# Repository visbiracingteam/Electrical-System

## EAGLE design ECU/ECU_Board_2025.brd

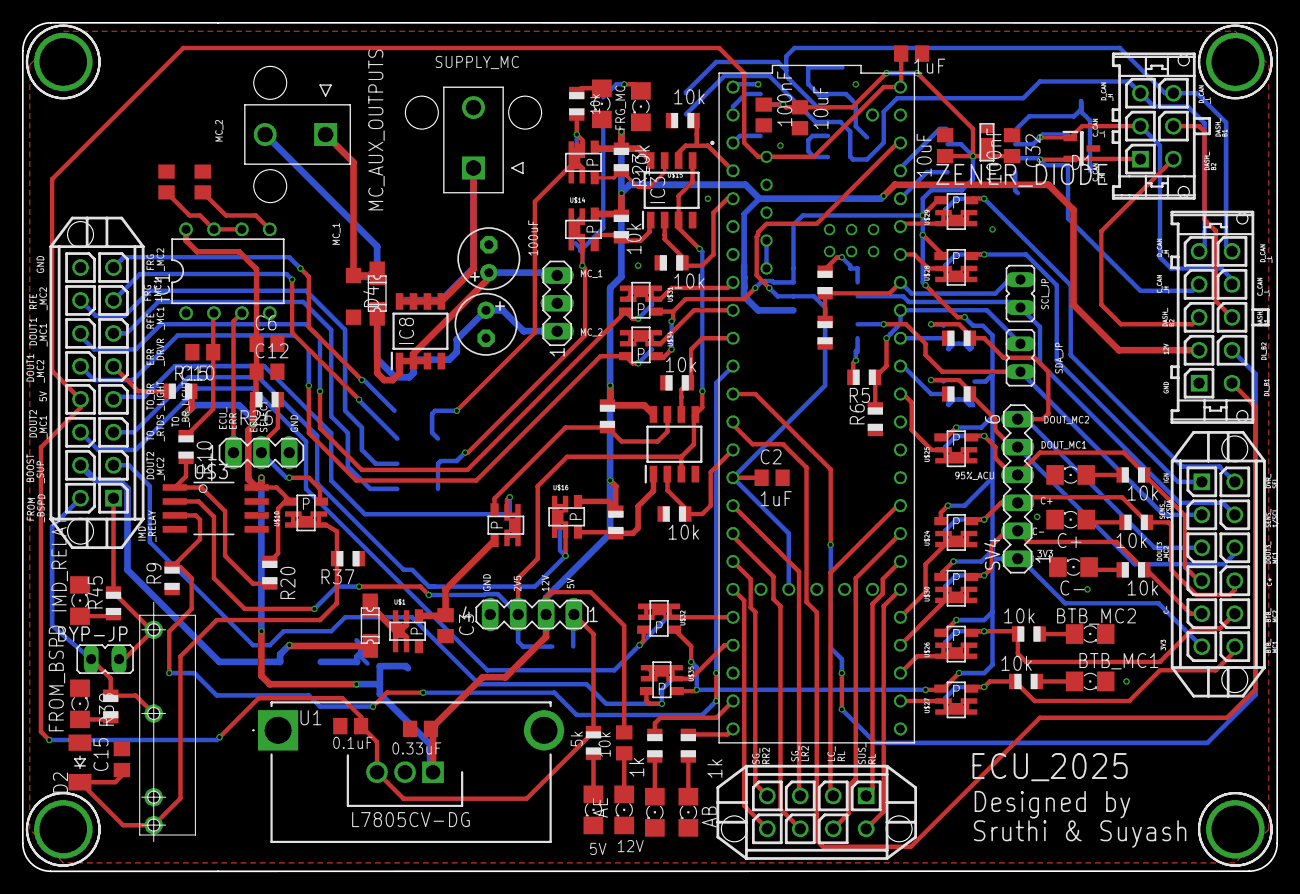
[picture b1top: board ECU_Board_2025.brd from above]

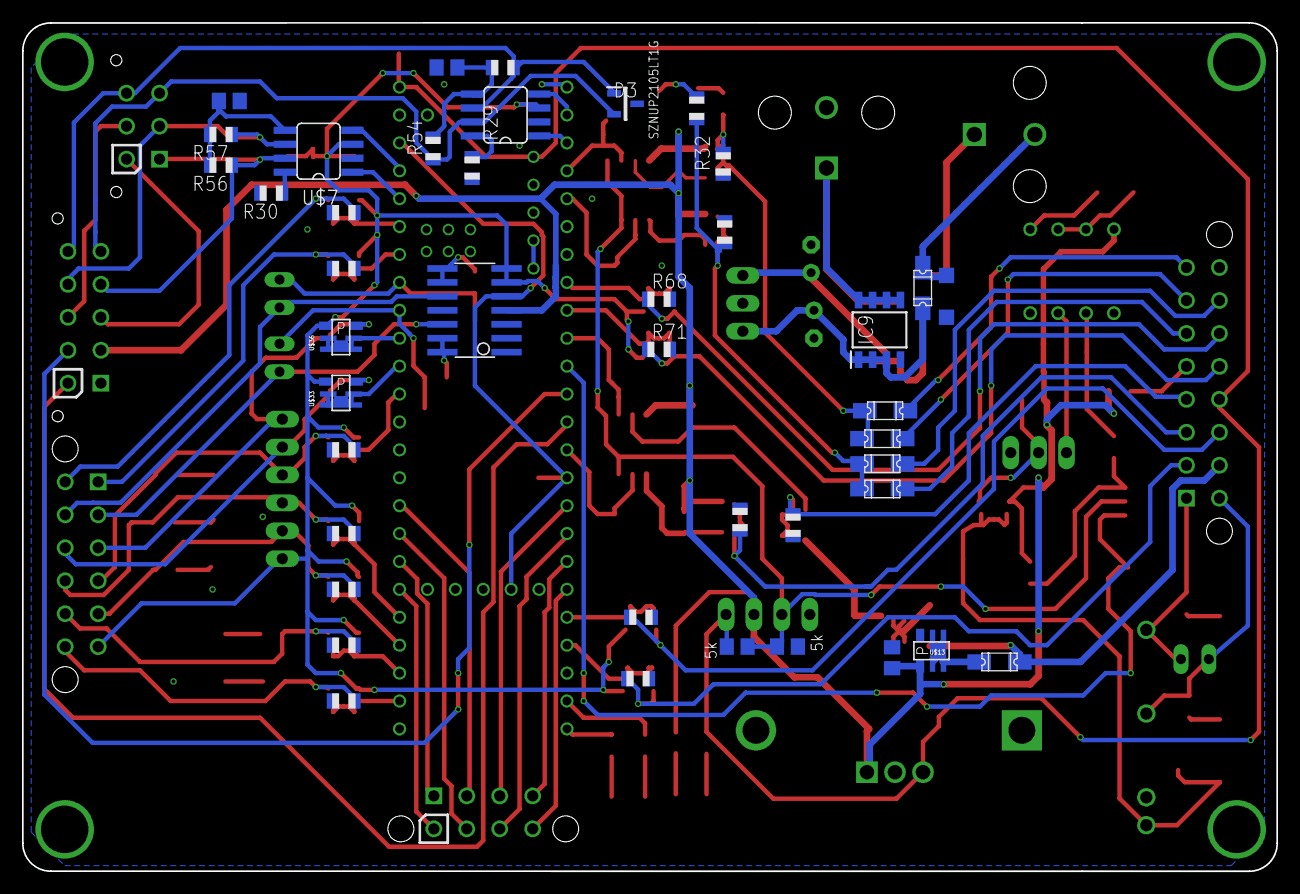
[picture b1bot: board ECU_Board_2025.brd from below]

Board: 2 copper layers, 114.2 x 77.2 mm, 150 parts (42 on the bottom side), 114 nets.

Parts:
5V, 12V: FKIT-LED-1206
>95%ACU: FKIT-LED-1206
AB: FKIT-LED-1206
AE: FKIT-LED-1206
BOOSTED_SUPPLY1: 172447-0002; 172447-YY02
BTB_MC1, BTB_MC2: FKIT-LED-1206
BYP-JP: JP1
C1, C2, C15: 1uF; C0805
C3, C4: C0805
C5, C35: 10uF; C0805
C6, C12, C13: 0.1uF; C0805
C7, C8: 100uF; E2,5-6
C10: 4.7uF; C0805
C11: 0.01uF; C0805
C32, C34: 100nF; C0805
C36, C37: 4n7F; C0805
C+: FKIT-LED-1206
C-: FKIT-LED-1206
D1, D3: SZNUP2105LT1G; SOT96P237X111-3N
D2: CGRM400-G; SOD-123_MINI-SMA
D4, D5: SOD123
DATA_LOGGER: 43045-1012
ECU_JPR: MA03-1
F1, F2, F3, F4, F5, F6, F7, F8: 1206L
FRG_MC: FKIT-LED-1206
FROM_BSPD: FKIT-LED-1206
IC1: LM555N; DIL08
IC2, IC3: NCV2903DR2G; SOIC127P600X175-8N
IC4: L7805CV-DG; TO255P460X1020X2008-3P
IC8, IC9: SI4425FDY-T1-GE3; SOIC127P600X175-8N
IMD_RELAY: FKIT-LED-1206
IN_CAP: 0.33uF; C0805
JP1, JP2: JP1
MC_AUX_OUTPUTS: 172447-0002; 172447-YY02
OUT_CAP: 0.1uF; C0805
R1, R7, R8, R9, R11, R12, R13, R14, R15, R16, R19, R22, R23, R24, R26, R27, R28, R31, R32, R34, R36, R38, R45, R52, R53: 10k; R0805
R2, R17, R21: 5k; R0805
R3, R5: 5K; R0805
R4, R6: 10K; R0805
R10: 200k; R0805
R20, R25, R33: 1k; R0805
R29, R30: 4k7; R0805
R37, R61, R62, R63, R64, R65, R66, R67, R68, R69, R70, R71, R72, R73: 100k; R0805
R54, R55, R56, R57: 60E; R0805
RFE_MC: FKIT-LED-1206
SV2: MA04-1
SV3: MA03-1
SV4: MA06-1
U1: HSS10-B20-P40; HSS10B20P40
U2: DEV-16771; MODULE_DEV-16771
U$1, U$10, U$13, U$14, U$15, U$16, U$17, U$24, U$25, U$26, U$27, U$28, U$29, U$30, U$31, U$32, U$33, U$34, U$35, U$36: TSOP-6_PMOS
U$2: LMC6464; SO14_LONGPADS
U$3: LMC6462; S08
U$7, U$8: SN65HVD230/1; SO8
U$9: G6DN_RELAY
U$20: ZENER_DIODE; SOD323HE
X1: 44769-0801
X2: 44769-1601
X3: 43045-0612
X4: 44769-1201

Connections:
2V5: IC2.3, IC2.5, IC3.3, IC3.5, R17.2, R21.1, SV2.3, U$3.2
3V3: C5.2, C32.2, C34.2, C35.2, SV4.1, U$2.6, U$2.7, U$7.3, U$8.3, U$20.CATHODE+, U$24.S, U$25.S, U$26.S, U$27.S, U$28.S, U$29.S, U$30.S, U$31.S, U$32.S, U$33.S, U$34.S, U$35.S, U$36.S, X4.P$6
3V3_TEENSY: C2.1, U2.3.3V_1, U2.3.3V_2, U2.3.3V_3, U$2.5
5V: C1.1, IC4.3, OUT_CAP.1, R2.2, R21.2, SV2.1, U2.5V, U2.VIN, X2.P$12
12V: C4.1, C6.1, C12.1, DATA_LOGGER.P$2, IC1.8, IC2.8, IC3.8, IC4.1, IN_CAP.1, R1.1, R15.2, R19.1, R20.1, R22.1, R23.1, R24.1, R26.2, SV2.2, U$2.4, U$3.8, U$10.S, U$13.S, U$14.S, U$15.S, U$16.S
>95%_ACU: R12.2, R66.1, SV4.4, U$25.G, X4.P$4
>95%_FINAL_3V3_INV: U2.15, U$25.1, U$25.2, U$25.5, U$25.6, U$25.D
AB: R25.2, U2.32
AE: R33.2, U2.31
AUXILIARY_VOLTAGE_MC1: D4.C, F3.P$1, MC_AUX_OUTPUTS.1
AUXILIARY_VOLTAGE_MC2: D5.C, F2.P$1, MC_AUX_OUTPUTS.2
BOOSTED_SUPPLY: F1.P$1, F8.P$1, X2.P$10
BR_LIGHT_SIG: IC2.6, R8.2, U2.8
BR_LIGHT_SUPPLY: C3.1, U$1.S, U$17.S
BTB_FROM_MC1: R27.2, R61.1, U$27.G, X4.P$12
BTB_FROM_MC1_3V3_INV: U2.34, U$27.1, U$27.2, U$27.5, U$27.6, U$27.D
BTB_FROM_MC2: R28.2, R62.1, U$26.G, X4.P$11
BTB_FROM_MC2_3V3_INV: U2.35, U$26.1, U$26.2, U$26.5, U$26.6, U$26.D
C+: R11.2, R63.1, SV4.3, U$24.G, X4.P$10
C+_3V3_INV: U2.37, U$24.1, U$24.2, U$24.5, U$24.6, U$24.D
C-: R13.2, R67.1, SV4.2, U$30.G, X4.P$5
C-_3V3_INV: U2.36, U$30.1, U$30.2, U$30.5, U$30.6, U$30.D
C_CAN_H: D1.2, DATA_LOGGER.P$4, R56.1, U$7.7, X3.P$1
C_CAN_L: D1.1, DATA_LOGGER.P$9, R57.1, U$7.6, X3.P$2
C_RX: U2.23, U$7.4
C_TX: U2.22, U$7.1
DASH_B1: DATA_LOGGER.P$8, X3.P$5
DASH_B2: DATA_LOGGER.P$3, X3.P$4
DL_B1: DATA_LOGGER.P$6, U2.11
DL_B2: DATA_LOGGER.P$7, U2.10
DOUT1_MC1: R68.1, U$31.G, X2.P$14
DOUT1_MC1_3V3: U2.6, U$31.1, U$31.2, U$31.5, U$31.6, U$31.D
DOUT1_MC2: R71.1, U$34.G, X2.P$13
DOUT1_MC2_3V3: U2.7, U$34.1, U$34.2, U$34.5, U$34.6, U$34.D
DOUT2_MC1: R69.1, U$32.G, X2.P$11
DOUT2_MC1_3V3: U2.28, U$32.1, U$32.2, U$32.5, U$32.6, U$32.D
DOUT2_MC2: R72.1, U$35.G, X2.P$2
DOUT2_MC2_3V3: U2.29, U$35.1, U$35.2, U$35.5, U$35.6, U$35.D
DOUT3_MC1: R70.1, SV4.5, U$33.G, X4.P$9
DOUT3_MC1_3V3: U2.16, U$33.1, U$33.2, U$33.5, U$33.6, U$33.D
DOUT3_MC2: R73.1, SV4.6, U$36.G, X4.P$3
DOUT3_MC2_3V3: U2.17, U$36.1, U$36.2, U$36.5, U$36.6, U$36.D
DRIVER_SELECT: R64.1, U$29.G, X4.P$7
DRIVER_SELECT_3V3_INV: U2.21, U$29.1, U$29.2, U$29.5, U$29.6, U$29.D
D_CAN_H: D3.2, DATA_LOGGER.P$5, R54.1, U$8.7, X3.P$3
D_CAN_L: D3.1, DATA_LOGGER.P$10, R55.1, U$8.6, X3.P$6
D_RX: U2.0, U$8.4
D_TX: U2.1, U$8.1
ECU_ERR: ECU_JPR.1, IC1.3
ECU_MC_ERR_SIG: R9.2, U2.9, U$3.3
ECU_SELECT: ECU_JPR.2, R26.1, U$10.G
ERR_RST_DRVR: R15.1, X2.P$5
FRG: IC3.6, R36.2, U2.2
FRG_MC: F4.P$1, F6.P$1, R16.2, R32.2, U$15.1, U$15.2, U$15.5, U$15.6, U$15.D
FRG_MC1: F6.P$2, X2.P$7
FRG_MC2: F4.P$2, X2.P$8
FROM_BSPD: BYP-JP.2, R38.2, U$9.P$3, X2.P$9
GND: 5V.C, 12V.C, >95%ACU.C, AB.C, AE.C, BOOSTED_SUPPLY1.2, BTB_MC1.C, BTB_MC2.C, C1.2, C2.2, C3.2, C4.2, C5.1, C6.2, C7.-, C8.-, C10.2, C11.2, C12.2, C13.2, C15.2, C32.1, C34.1, C35.1, C36.2, C37.2, C+.C, C-.C, D1.3, D2.A, D3.3, D4.A, D5.A, DATA_LOGGER.P$1, ECU_JPR.3, FRG_MC.C, FROM_BSPD.C, IC1.1, IC2.4, IC3.4, IC4.2, IC8.4, IC9.4, IMD_RELAY.C, IN_CAP.2, OUT_CAP.2, R4.1, R6.1, R7.1, R8.1, R9.1, R17.1, R29.2, R30.2, R31.1, R32.1, R34.1, R36.1, R37.1, R52.1, R53.1, R61.2, R62.2, R63.2, R64.2, R65.2, R66.2, R67.2, R68.2, R69.2, R70.2, R71.2, R72.2, R73.2, RFE_MC.C, SV2.4, U2.GND1, U2.GND2, U2.GND3, U2.GND4, U2.GND5, U$1.G, U$2.11, U$3.4, U$7.2, U$8.2, U$9.P$2, U$13.G, U$20.ANODE-, X2.P$16
IGNITION_SWITCH: R65.1, U$28.G, X4.P$1
IGNITION_SWITCH_3V3_INV: U2.20, U$28.1, U$28.2, U$28.5, U$28.6, U$28.D
IMD_RELAY: BYP-JP.1, R45.2, U$9.P$4, X2.P$1
LC_RL: U2.41, X1.P$2
LC_RR: U2.40, X1.P$6
MC_1: C7.+, F3.P$2, IC8.1, IC8.2, IC8.3, SV3.3
MC_2: C8.+, F2.P$2, IC9.1, IC9.2, IC9.3, SV3.1
unnamed: 12V.A, R1.2
unnamed: R14.1, RFE_MC.A
unnamed: AB.A, R25.1
unnamed: FRG_MC.A, R16.1
unnamed: IC2.1, R22.2, U$16.G
unnamed: 5V.A, R2.1
unnamed: IC2.7, R19.2, U$17.G
unnamed: AE.A, R33.1
unnamed: F8.P$2, U$1.1, U$1.2, U$1.5, U$1.6, U$1.D
unnamed: C10.1, IC1.2, R10.1
unnamed: C11.1, IC1.5
unnamed: R10.2, R20.2, U$3.1
unnamed: C+.A, R11.1
unnamed: >95%ACU.A, R12.1
unnamed: C-.A, R13.1
unnamed: BTB_MC1.A, R27.1
unnamed: C13.1, IC1.6, IC1.7
unnamed: IMD_RELAY.A, R45.1
unnamed: FROM_BSPD.A, R38.1
unnamed: BTB_MC2.A, R28.1
unnamed: R29.1, U$8.8
unnamed: C37.1, R54.2, R55.2, U$8.5
unnamed: C36.1, R56.2, R57.2, U$7.5
unnamed: R30.1, U$7.8
unnamed: F1.P$2, U$13.1, U$13.2, U$13.5, U$13.6, U$13.D
NET1: R3.2, U$2.8, U$2.9
NET2: R5.2, U$2.13, U$2.14
RFE: IC3.2, R34.2, U2.3
RFE_MC: F5.P$1, F7.P$1, R14.2, R31.2, U$14.1, U$14.2, U$14.5, U$14.6, U$14.D
RFE_MC1: F5.P$2, X2.P$6
RFE_MC2: F7.P$2, X2.P$15
RTDS_SIG: IC2.2, R7.2, U2.12
SENS_1/SCL: JP2.1, U$2.10, X4.P$8
SENS_1/SCL_OUT: JP2.2, R3.1, R4.2, U2.19
SENS_1/SDA: JP1.2, U$2.12, X4.P$2
SENS_1/SDA_OUT: JP1.1, R5.1, R6.2, U2.18
SG_LR1: U2.25, X1.P$7
SG_LR2: U2.24, X1.P$3
SG_RR1: U2.27, X1.P$8
SG_RR2: U2.26, X1.P$4
SUPPLY_MC: BOOSTED_SUPPLY1.1, IC8.5, IC8.6, IC8.7, IC8.8, IC9.5, IC9.6, IC9.7, IC9.8
SUS_RL: U2.39, X1.P$1
SUS_RR: U2.38, X1.P$5
TO_BR_LIGHT: R53.2, U$17.1, U$17.2, U$17.5, U$17.6, U$17.D, X2.P$4
TO_ECU_RELAY: C15.1, D2.C, R37.2, U$9.P$1, U$10.1, U$10.2, U$10.5, U$10.6, U$10.D
TO_FRG_ENABLE: IC3.7, R23.2, U$15.G
TO_RFE_ENABLE: IC3.1, R24.2, U$14.G
TO_RTDS: R52.2, U$16.1, U$16.2, U$16.5, U$16.6, U$16.D, X2.P$3
USB_GND: U2.USB_GND1, U2.USB_GND2

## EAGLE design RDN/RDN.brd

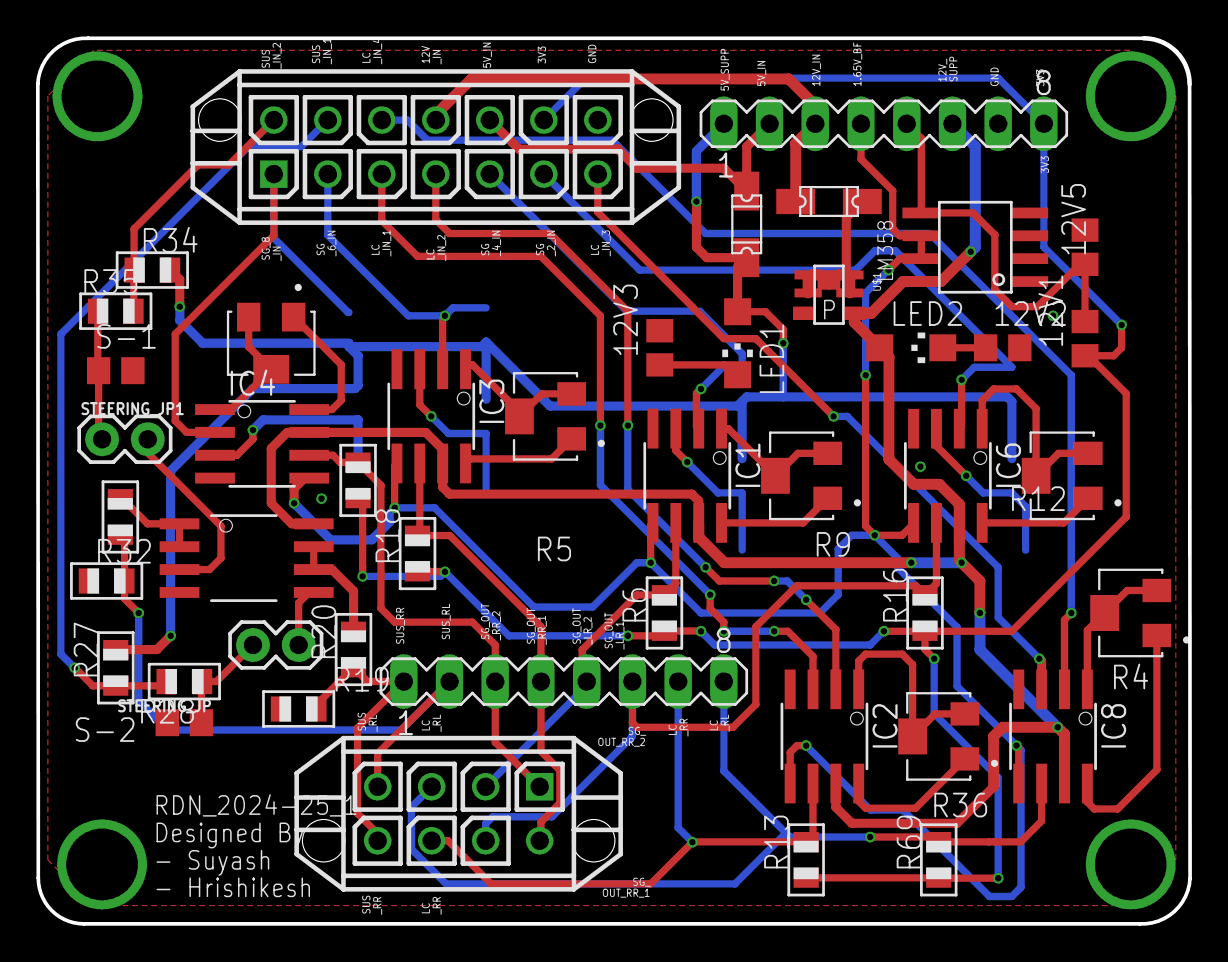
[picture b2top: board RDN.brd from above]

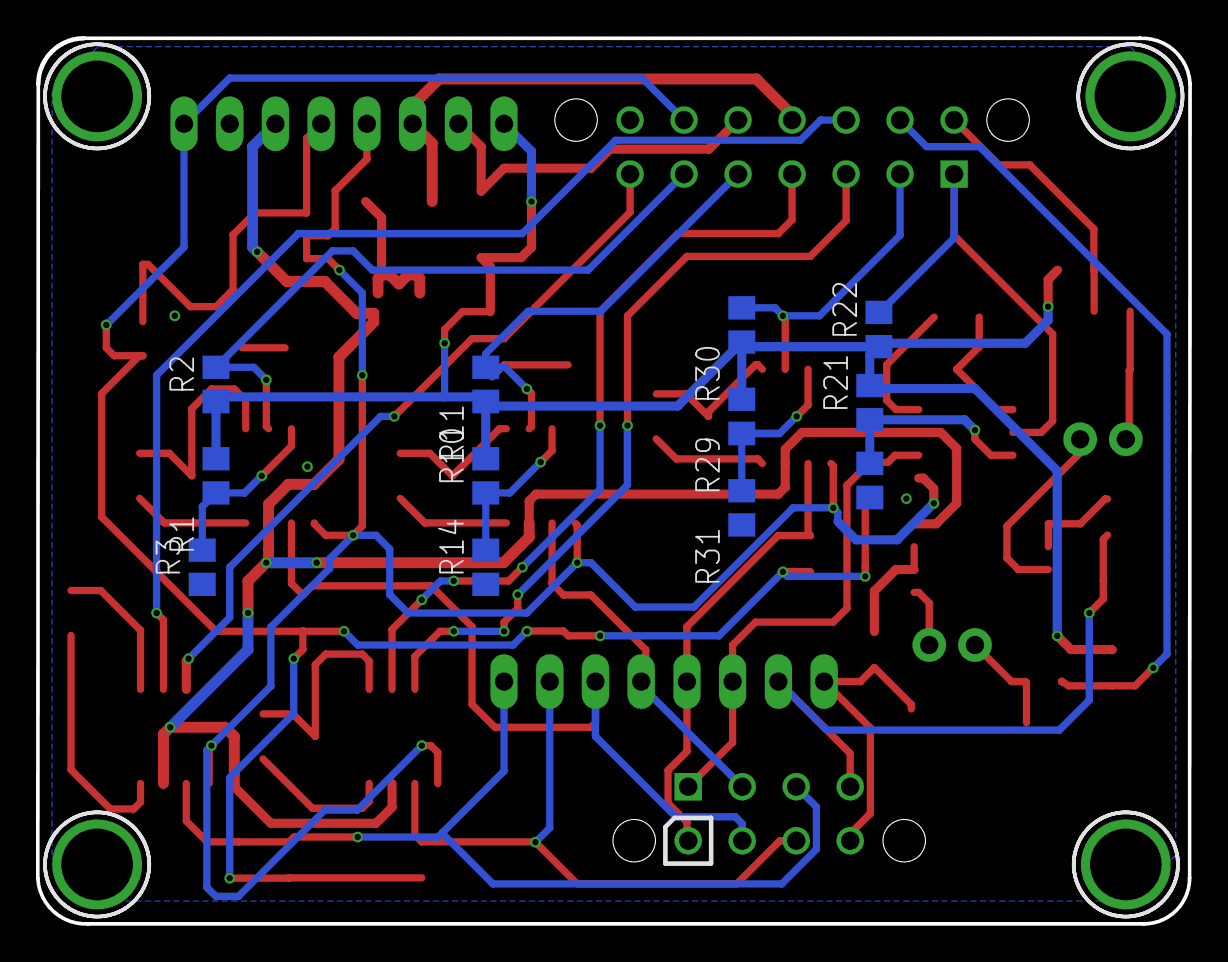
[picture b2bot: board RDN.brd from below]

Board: 2 copper layers, 64.0 x 49.2 mm, 57 parts (12 on the bottom side), 51 nets.

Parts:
12V1, 12V5: 10k; R0805
12V2: 2k; R0805
12V3: 6k; R0805
F1, F5: 1206L
IC1, IC2, IC3, IC4, IC6, IC8: INA122U; SO08
LED1, LED2: CHIPLED_1206
LM358: LM358EDR2G; SOIC-8
R1, R2, R3, R10, R11, R14, R21, R22, R23, R29, R30, R31: 120; R0805
R4, R5, R7, R9, R12, R36: PVG5A103C03R00; TRIM_PVG5A103C03R00
R6, R13, R16, R18, R26, R28, R35, R69: 1k; R0805
R19, R32: 10k; R0805
R20, R33: 5k; R0805
R27, R34: 300k; R0805
S-1, S-2: 1uF; C0805
STEERING_JP, STEERING_JP1: STEERING_JP; 1X02
SV1, SV4: MA08-1
U$1: TSOP-6_PMOS
U$2: LMC6462; S08
X3: 44769-0801
X4: 44769-1401

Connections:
1.65V_REF: 12V1.2, 12V5.1, LM358.5, SV1.5
1.65V_REF_BF: IC1.5, IC2.5, IC3.5, IC4.5, IC6.5, IC8.5, LM358.6, LM358.7, SV1.4
3V3: 12V1.1, R6.1, R13.1, R16.1, R18.1, R26.1, R69.1, SV1.8, X4.P$13
5V_IN: F5.P$2, SV1.2, X4.P$12
5V_SUPPLY: F5.P$1, LED1.A, R1.2, R2.1, R10.2, R11.1, R21.2, R22.1, R27.2, R29.2, R30.1, R34.2, SV1.1
12V_IN: F1.P$2, SV1.3, X4.P$11
12V_SUPPLY: IC1.7, IC2.7, IC3.7, IC4.7, IC6.7, IC8.7, LED2.A, LM358.8, SV1.6, U$1.S, U$2.8
GND: 12V2.2, 12V3.2, 12V5.2, IC1.4, IC2.4, IC3.4, IC4.4, IC6.4, IC8.4, LM358.4, R3.1, R14.1, R19.1, R23.1, R31.1, R32.1, S-1.2, S-2.2, SV1.7, U$1.G, U$2.4, X4.P$14
LC_RL: IC8.6, R69.2, SV4.8, X3.P$3
LC_RR: IC2.6, R13.2, SV4.7, X3.P$7
LOADCELL_IN_1: IC2.3, X4.P$3
LOADCELL_IN_2: IC2.2, X4.P$4
LOADCELL_IN_3: IC8.3, X4.P$7
LOADCELL_IN_4: IC8.2, X4.P$10
N1: STEERING_JP1.2, U$2.3
N2: STEERING_JP.2, U$2.5
unnamed: IC1.1, R9.2, R9.3
unnamed: IC1.8, R9.1
unnamed: 12V2.1, LED2.C
unnamed: IC2.1, R36.2, R36.3
unnamed: IC2.8, R36.1
unnamed: IC3.1, R5.2, R5.3
unnamed: IC3.8, R5.1
unnamed: R20.2, U$2.6, U$2.7
unnamed: R28.1, S-2.1, STEERING_JP.1
unnamed: IC4.1, R7.2, R7.3
unnamed: IC4.8, R7.1
unnamed: R33.2, U$2.1, U$2.2
unnamed: R35.1, S-1.1, STEERING_JP1.1
unnamed: IC6.1, R12.2, R12.3
unnamed: IC6.8, R12.1
unnamed: 12V3.1, LED1.C
unnamed: IC8.1, R4.2, R4.3
unnamed: IC8.8, R4.1
unnamed: F1.P$1, U$1.1, U$1.2, U$1.5, U$1.6, U$1.D
SG_1_IN: IC6.3, R1.1, R3.2
SG_2_IN: IC6.2, R2.2, X4.P$6
SG_3_IN: IC1.3, R10.1, R14.2
SG_4_IN: IC1.2, R11.2, X4.P$5
SG_5_IN: IC3.3, R29.1, R31.2
SG_6_IN: IC3.2, R30.2, X4.P$2
SG_7_IN: IC4.3, R21.1, R23.2
SG_8_IN: IC4.2, R22.2, X4.P$1
SG_OUT_LR_1: IC6.6, R16.2, SV4.6, X3.P$6
SG_OUT_LR_2: IC1.6, R6.2, SV4.5, X3.P$2
SG_OUT_RR_1: IC3.6, R18.2, SV4.4, X3.P$5
SG_OUT_RR_2: IC4.6, R26.2, SV4.3, X3.P$1
SUS_IN_1: R27.1, R28.2, X4.P$9
SUS_IN_2: R34.1, R35.2, X4.P$8
SUS_RL: R32.2, R33.1, SV4.2, X3.P$4
SUS_RR: R19.2, R20.1, SV4.1, X3.P$8
